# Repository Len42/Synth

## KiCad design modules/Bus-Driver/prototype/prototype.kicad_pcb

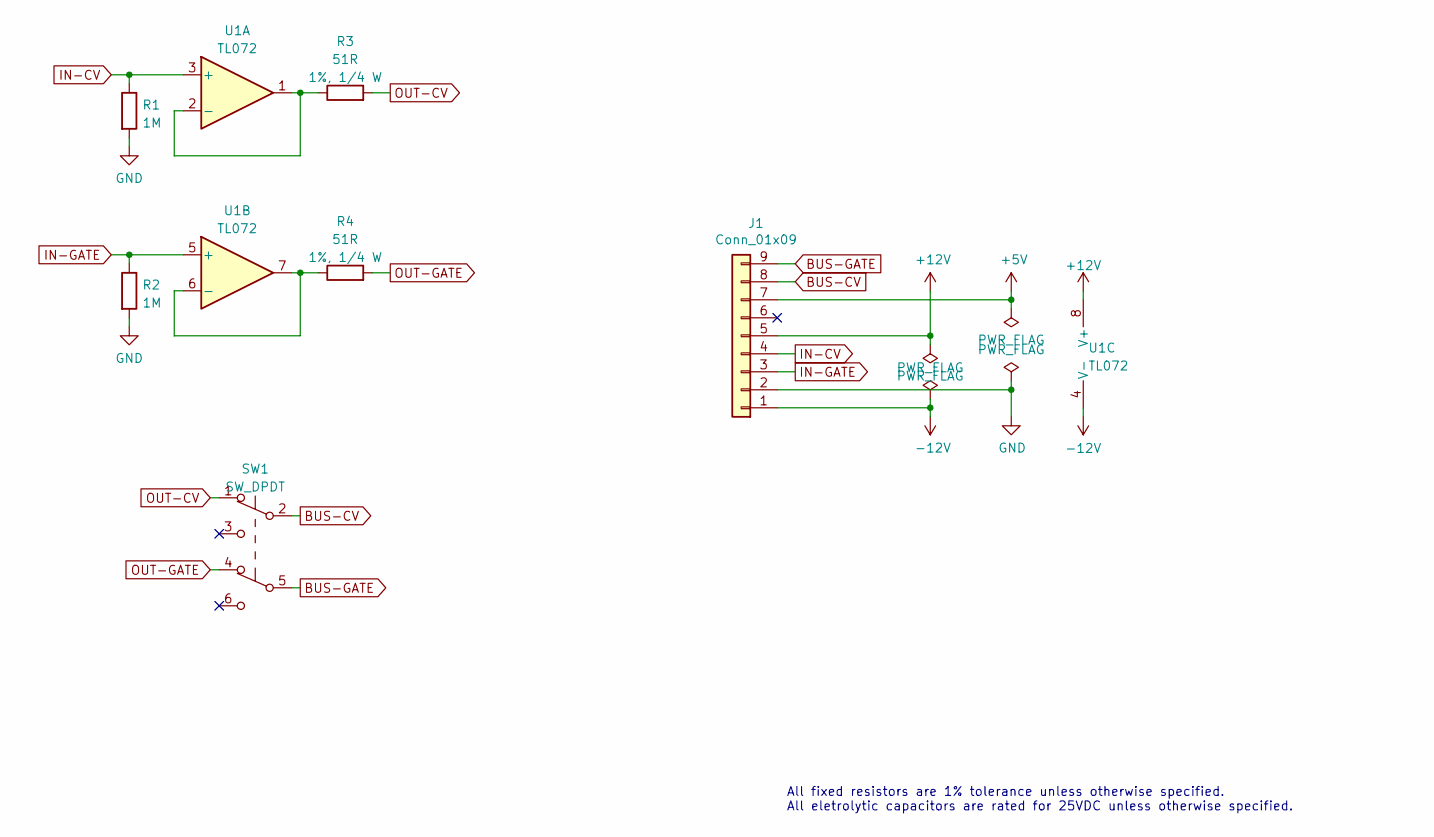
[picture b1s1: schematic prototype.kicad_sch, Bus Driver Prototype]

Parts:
J1: Conn_01x09; PinHeader_1x09_P2.54mm_Vertical
R1, R2: 1M; R_Axial_DIN0207_L6.3mm_D2.5mm_P7.62mm_Horizontal; ManufacturerPartNum MFR-12*
R3, R4: 51R; R_Axial_DIN0207_L6.3mm_D2.5mm_P10.16mm_Horizontal; ManufacturerPartNum MFR-25FBF52-51R
SW1: SW_DPDT; SW_DPDT_THT_2.54; ManufacturerPartNum 2S1-MDP1-T1-B1-M2QE
U1: TL072; DIP-8_W7.62mm; ManufacturerPartNum TL072BCP

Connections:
+5V: J1.7
+12V: J1.5, U1.8 (V+)
-12V: J1.1, U1.4 (V-)
BUS-CV: J1.8, SW1.2 (B)
BUS-GATE: J1.9, SW1.5 (B)
GND: J1.2, R1.2, R2.2
IN-CV: J1.4, R1.1, U1.3 (+)
IN-GATE: J1.3, R2.1, U1.5 (+)
unnamed: R3.1, U1.1, U1.2 (-)
unnamed: R4.1, U1.6 (-), U1.7
OUT-CV: R3.2, SW1.1 (A)
OUT-GATE: R4.2, SW1.4 (A)

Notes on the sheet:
All fixed resistors are 1% tolerance unless otherwise specified. All eletrolytic capacitors are rated for 25VDC unless otherwise specified.

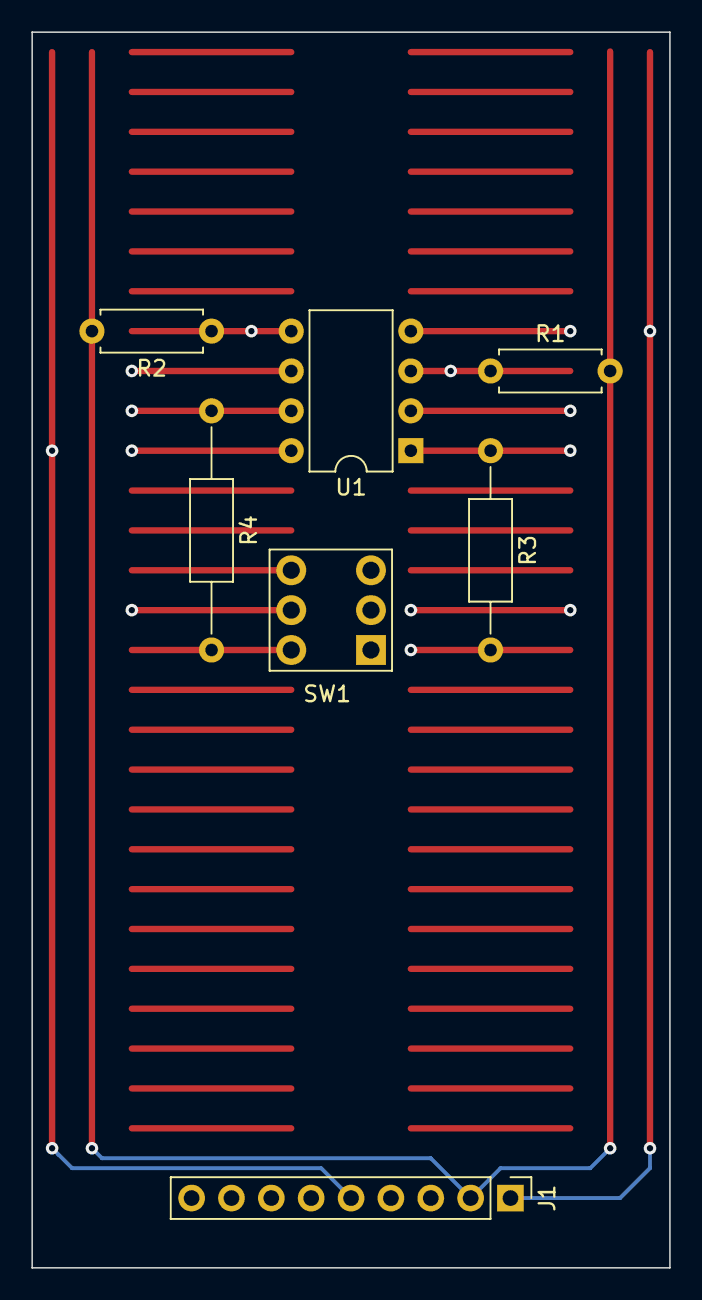
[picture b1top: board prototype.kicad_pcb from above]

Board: 6 copper layers, 40.6 x 78.7 mm, 7 parts (0 on the bottom side), 11 nets.

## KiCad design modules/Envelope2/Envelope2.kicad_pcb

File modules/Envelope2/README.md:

# Dual Envelope Generator

## 8HP Eurorack Module

### Features
- Two ADSR envelope generators
- Attack, decay, and release times range from very short (< 1 millisecond) to approx. 10 seconds
- Envelopes are switchable between linear and logarithmic curves
- Gate input can default to the Eurorack bus gate line (jumper-selectable) - more info [here](https://lenp.net/synth/eurorack-bus-cv-gate.html)
- Channel 1 gate input is normalled to channel 2 so one gate signal can trigger both envelopes

### Notes
This module requires a 16-pin Eurorack power cable that supplies +5 V power in addition to +12 V and -12 V.

An Arduino-compatible ATmega328P microcontroller generates the envelopes. The firmware source code is in [firmware/Envelope2/Envelope2.ino](firmware/Envelope2/Envelope2.ino). MakeLookupTables is a program that generates data tables used in the firmware. See [here](https://lenp.net/synth/firmware-programming.html) for info about programming the firmware onto the microcontroller chip.

PCB layouts are provided in KiCad and gerber formats. A front panel design is included as a drilled PCB layout (with no labels or graphics).

The PCBs that I used can be ordered from OSH Park. The designs are here:
- [Front panel](https://oshpark.com/shared_projects/PnWXqRcs)
- [Controls board](https://oshpark.com/shared_projects/XBUi1v48)
- [Main board](https://oshpark.com/shared_projects/cbrPcghP) (Note: There is an error in this PCB which has been corrected in the current version of the KiCad & gerber files.)

Please note that I am a hobbyist, not a trained electronics engineer. No guarantees!

### Software Used

* [KiCad](https://www.kicad.org/) 6.0.0
* [Arduino](https://www.arduino.cc/) 1.8.18
* (optional) [Visual Studio 2019](https://visualstudio.microsoft.com/) - Only used to generate the numtables.h file, which is provided.

<hr /><div><div style="float:left; padding-right:10px;"></div><div style="xfloat:left; padding-left:10px;"><br />© 2022 Len Popp CC BY<br />This work is licensed under a <a rel="license" href="http://creativecommons.org/licenses/by/4.0/">Creative Commons Attribution 4.0 International License</a>.</div></div>

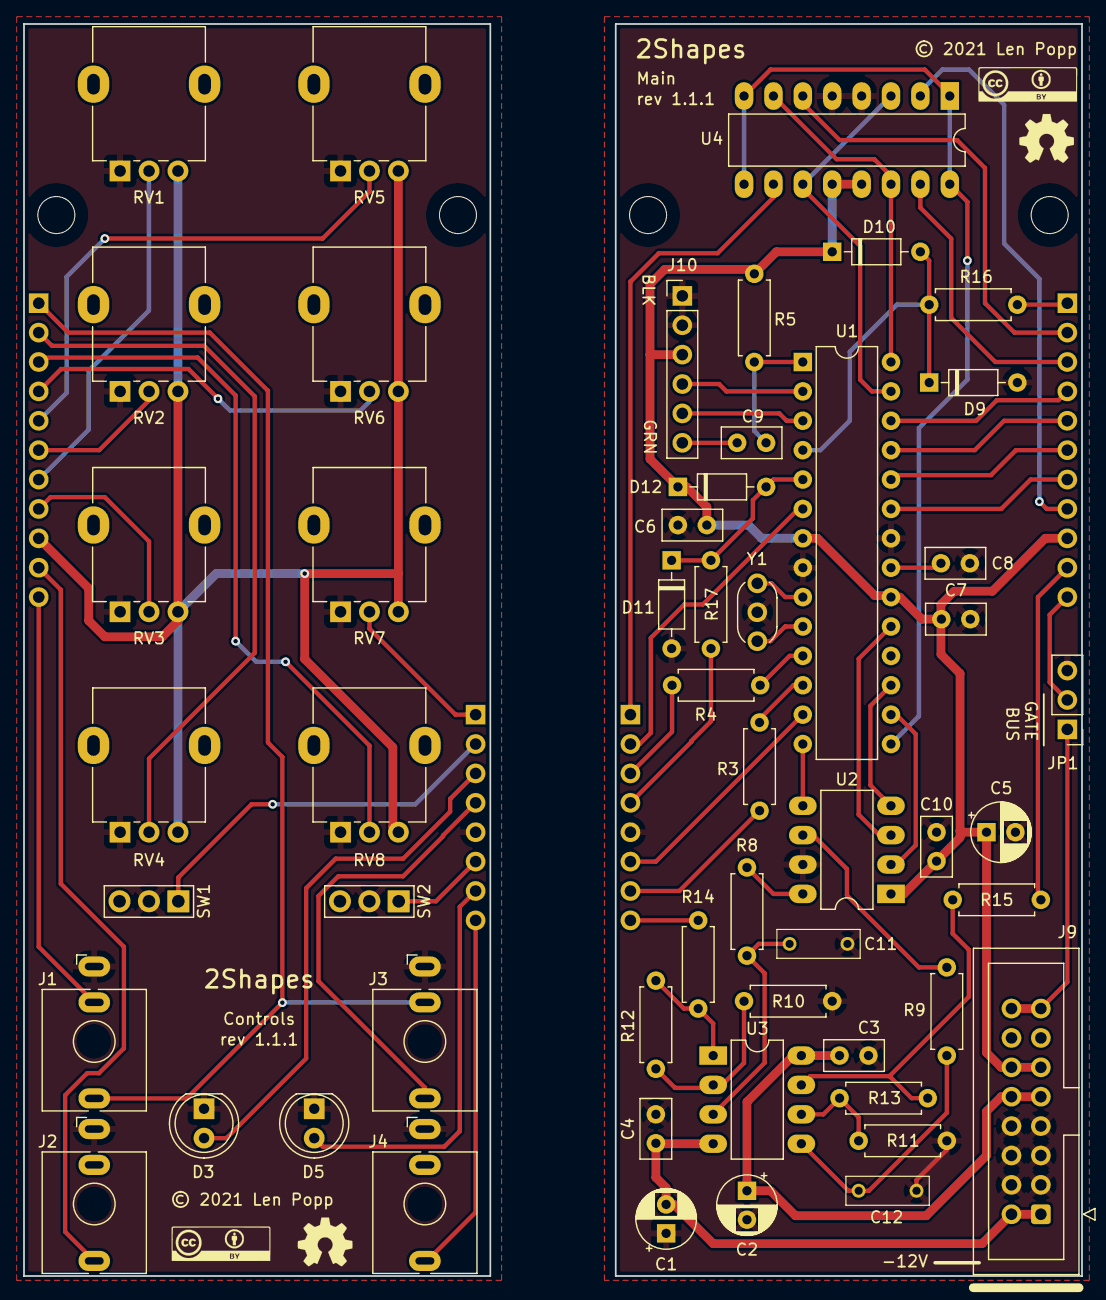
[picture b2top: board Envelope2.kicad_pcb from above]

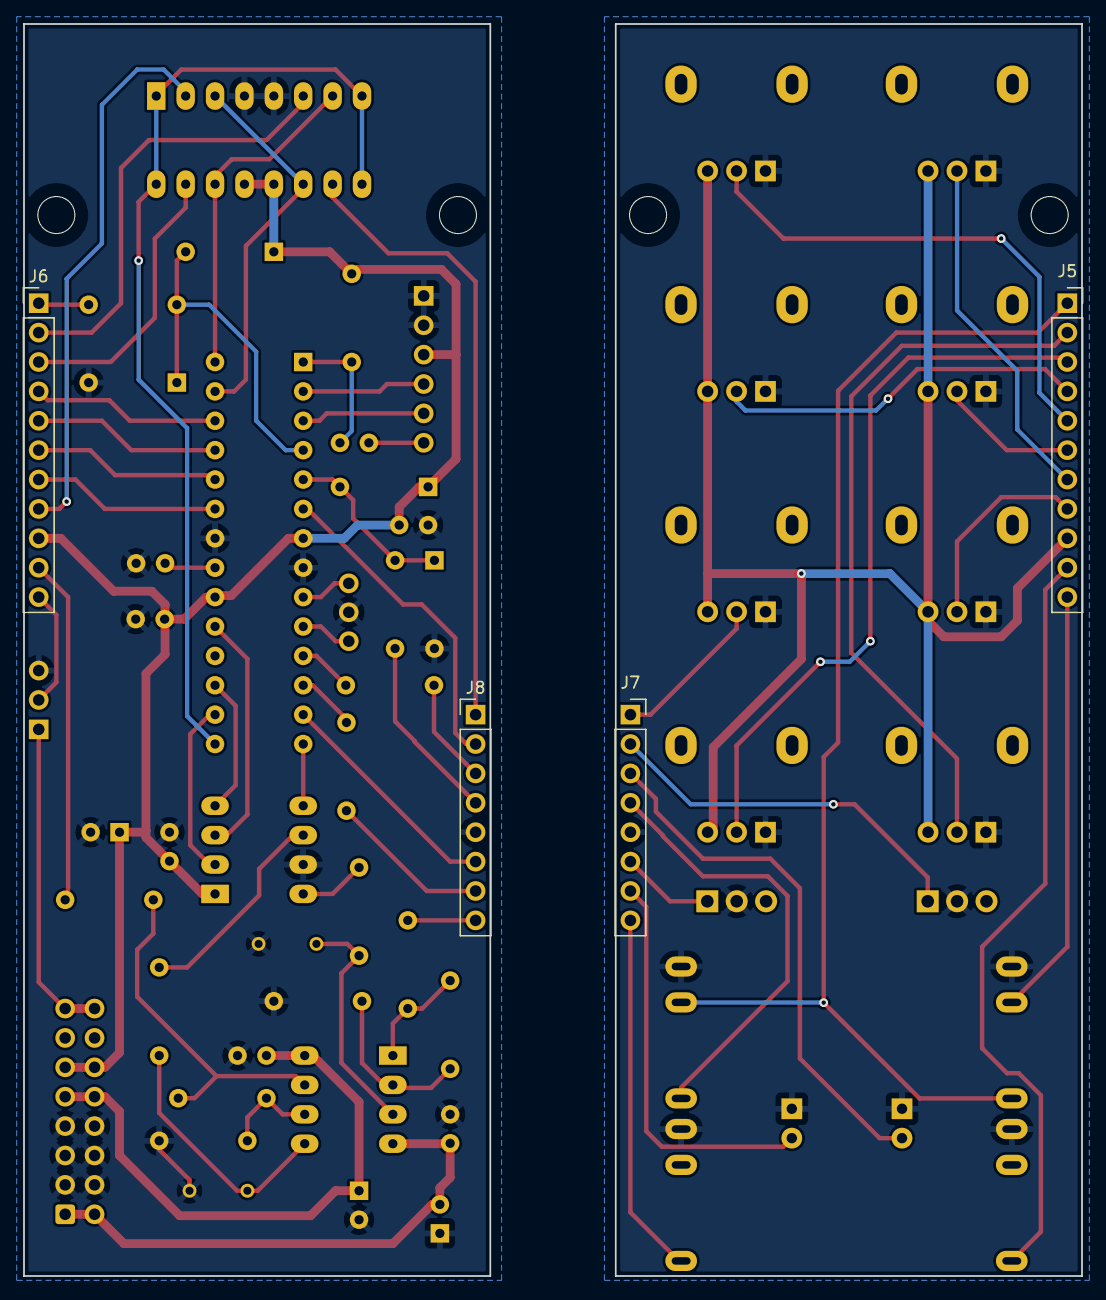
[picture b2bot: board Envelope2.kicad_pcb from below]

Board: 2 copper layers, 91.4 x 108.2 mm, 65 parts (4 on the bottom side), 48 nets.

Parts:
C1, C2, C5: 10U; CP_Radial_D5.0mm_P2.50mm
C3, C4, C6, C7, C8, C9, C10: 100N; C_Disc_D5.0mm_W2.5mm_P2.50mm
C11, C12: 3N3; C_Rect_Kemet_L7.2mm_W2.5mm_P5mm
D3, D5: LED_5mm_Blue; LED_D5.0mm
D9, D10, D11, D12: 1N5711; D_DO-35_SOD27_P7.62mm_Horizontal
G1, G2: Logo_CC_BY
G3, G4: Logo_OSHW
H1, H2, H3, H4: MountingHole_M3; MountingHole_PCB_3.2mm_M3
J1, J2, J3, J4: WQP-PJ398; Jack_3.5mm_QingPu_WQP-PJ398SM_Vertical
J5: Conn_Front_Left_Top; PinSocket_1x11_P2.54mm_Vertical
J6: Conn_Back_Right_Top; PinHeader_1x11_P2.54mm_Vertical
J7: Conn_Front_Right; PinSocket_1x08_P2.54mm_Vertical
J8: Conn_Back_Left; PinHeader_1x08_P2.54mm_Vertical
J9: Conn_Eurorack_16; IDC-Header-Eurorack-16-TH
J10: FTDI; PinHeader_1x06_P2.54mm_Vertical
JP1: GATE-BUS; PinHeader_1x03_P2.54mm_Vertical
R3, R4: 270R; R_Axial_DIN0207_L6.3mm_D2.5mm_P7.62mm_Horizontal
R5: 10K; R_Axial_DIN0207_L6.3mm_D2.5mm_P7.62mm_Horizontal
R8, R9: 24K; R_Axial_DIN0207_L6.3mm_D2.5mm_P7.62mm_Horizontal
R10, R11, R12, R13: 47K; R_Axial_DIN0207_L6.3mm_D2.5mm_P7.62mm_Horizontal
R14, R15: 51R; R_Axial_DIN0207_L6.3mm_D2.5mm_P7.62mm_Horizontal
R16, R17: 100K; R_Axial_DIN0207_L6.3mm_D2.5mm_P7.62mm_Horizontal
RV1, RV2, RV3, RV4, RV5, RV6, RV7, RV8: 100K; Potentiometer_Alpha_RD901F-40-00D_Single_Vertical
SW1, SW2: SPDT; SW_SPDT_THT_2.54
U1: ATmega328P-PU; DIP-28_W7.62mm
U2: MCP4822; DIP-8_W7.62mm_LongPads
U3: TL072; DIP-8_W7.62mm_LongPads
U4: DG413; DIP-16_W7.62mm_LongPads
Y1: 16MHz; Resonator_muRata_CSTLSxxxX-3Pin_W5.5mm_H3.0mm

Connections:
+5V: C5.1, C6.1, C7.1, C10.2, D10.1 (K), D12.1 (K), J5.9, J6.9, J9.11 (+5V), J9.12, J10.3 (VCC), R5.1, RV1.3, RV2.3, RV3.3, RV4.3, RV5.3, RV6.3, RV7.3, RV8.3, U1.7 (VCC), U1.20 (AVCC), U2.1 (Vdd), U4.12 (VL), U4.13 (V+)
+12V: C2.1, C3.1, J9.9 (+12V), J9.10, U3.8 (V+)
-12V: C1.2, C4.2, J9.1 (-12V), J9.2, U3.4 (V-)
/Main/ADC-SEL: U1.15 ((PCINT1/OC1A/PB1)d9), U4.1, U4.8, U4.9, U4.16
/Main/SPI-MOSI: U1.17 ((PCINT3/OC2A/MOSI/PB3)d11), U2.4 (SDI)
/Main/SPI-SCLK: U1.19 ((PCINT5/SCK/PB5)d13), U2.3 (SCK)
/Main/UART_RX: J10.4 (TXO), U1.2 ((PCINT16/RXD/PD0)d0)
/Main/UART_TX: J10.5 (RXI), U1.3 ((PCINT17/TXD/PD1)d1)
/Main/~LDAC: U1.14 ((PCINT0/CLKO/ICP1/PB0)d8), U2.5 (~LDAC)
/Main/~RESET: C9.2, R5.2, U1.1 ((PCINT14/~RESET/)PC6)
/Main/~SPI-CS: U1.16 ((PCINT2/OC1B/~SS/PB2)d10), U2.2 (~CS)
GATE-1: D9.1 (K), D10.2 (A), R16.1, U1.4 ((PCINT18/INT0/PD2)d2)
GATE-2: D11.1 (K), D12.2 (A), R17.1, U1.5 ((PCINT19/OC2B/INT1/PD3)d3)
GND: C1.1, C2.2, C3.2, C4.1, C5.2, C6.2, C7.2, C8.2, C10.1, C11.2, C12.2, D3.1 (K), D5.1 (K), D9.2 (A), D11.2 (A), J1.S, J2.S, J3.S, J4.S, J7.5, J8.5, J9.3 (GND), J9.4, J9.5 (GND), J9.6, J9.7 (GND), J9.8, J10.1 (GND), J10.2 (CTS), JP1.3 (B), R10.2, R11.2, RV1.1, RV2.1, RV3.1, RV4.1, RV5.1, RV6.1, RV7.1, RV8.1, SW1.2 (B), SW2.2 (B), U1.8 (GND), U1.22 (GND), U2.7 (Vss), U4.4 (V-), U4.5 (GND), Y1.2
IN-GATE-1: J1.T, J3.TN, J5.1, J6.1, R16.2
IN-GATE-2: J3.T, J7.4, J8.4, R17.2
IN-GATE-BUS: J1.TN, J5.11, J6.11, JP1.2 (C)
IN-POT-A-1: J5.7, J6.7, RV1.2, U1.23 ((PCINT8/ADC0/PC0)a0)
IN-POT-A-2: J5.5, J6.5, RV5.2, U1.25 ((PCINT10/ADC2/PC2)a2)
IN-POT-D-1: J5.6, J6.6, RV2.2, U1.24 ((PCINT9/ADC1/PC1)a1)
IN-POT-D-2: J5.4, J6.4, RV6.2, U1.26 ((PCINT11/ADC3/PC3)a3)
IN-POT-R-1: J5.2, J6.2, RV4.2, U4.6
IN-POT-R-2: J5.3, J6.3, RV8.2, U4.15
IN-POT-R-BOTH: U1.28 ((PCINT13/SCL/ADC5/PC5)a5), U4.7, U4.14
IN-POT-S-1: J5.8, J6.8, RV3.2, U4.2
IN-POT-S-2: J7.1, J8.1, RV7.2, U4.10
IN-POT-S-BOTH: U1.27 ((PCINT12/SDA/ADC4/PC4)a4), U4.3, U4.11
IN-SW-LOGLIN-1: J7.2, J8.2, SW1.1 (A), U1.6 ((PCINT20/XCK/T0/PD4)d4)
IN-SW-LOGLIN-2: J7.6, J8.6, SW2.1 (A), U1.13 ((PCINT23/AIN1/PD7)d7)
LED-1: D3.2 (A), J7.3, J8.3, R4.2
LED-2: D5.2 (A), J7.7, J8.7, R3.2
unnamed: C8.1, U1.21 (AREF)
unnamed: C9.1, J10.6 (DTR)
unnamed: C11.1, R8.1, U3.3 (+)
unnamed: C12.1, R9.1, U3.5 (+)
unnamed: J9.15 (GATE), J9.16, JP1.1 (A)
unnamed: R3.1, U1.12 ((PCINT22/OC0A/AIN0/PD6)d6)
unnamed: R4.1, U1.11 ((PCINT21/OC0B/T1/PD5)d5)
unnamed: R8.2, U2.8 (VA)
unnamed: R9.2, U2.6 (VB)
unnamed: R10.1, R12.2, U3.2 (-)
unnamed: R11.1, R13.2, U3.6 (-)
unnamed: R12.1, R14.2, U3.1
unnamed: R13.1, R15.2, U3.7
unnamed: U1.9 ((PCINT6/TOSC1/PB6)XTAL1), Y1.3
unnamed: U1.10 ((PCINT7/TOSC2/PB7)XTAL2), Y1.1
OUT-1: J2.T, J5.10, J6.10, R15.1
OUT-2: J4.T, J7.8, J8.8, R14.1

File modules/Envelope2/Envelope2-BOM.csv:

Ref,Qty,Value,Value2,Note,Description,Datasheet,Manufacturer,ManuPartNum,Distributor1,DistributorPartNum1,DistributorPartLink1,Distributor2,DistributorPartNum2,DistributorPartLink2,Distributor3,DistributorPartNum3,DistributorPartLink3
A1,1,Cable_Eurorack_16,,Length as required,Eurorack 16-16 pin power & bus cable,,,,Thonk,,https://www.thonk.co.uk/shop/eurorack-power-cables/,SynthCube,,https://synthcube.com/cart/eurorack-ribbon-power-cables,Modular Addict,,https://modularaddict.com/parts/eurorack-power-cables-1
C1 C2 C5,3,10U,25 VDC,12 V decoupling,Capacitor - Electrolytic - 12 V decoupling,https://industrial.panasonic.com/cdbs/www-data/pdf/RDF0000/A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,Panasonic,EEA-FC1E100,Mouser,667-EEA-FC1E100,https://www.mouser.ca/ProductDetail/Panasonic/EEA-FC1E100?qs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,,,,,,
C3 C4 C6 C7 C8 C9 C10,7,100N,,IC decoupling,Capacitor - Ceramic - IC decoupling,,TDK,FG18X7R1H104KNT06,Mouser,810-FG18X7R1H104KNT6,https://www.mouser.ca/ProductDetail/810-FG18X7R1H104KNT6,,,,,,
C11 C12,2,3N3,,,Capacitor - Film,https://www.mouser.ca/datasheet/2/212/F3294_MMK-1101858.pdf,KEMET,MMK5102J100J01L16.5TA18,Mouser,80-MMK5102J100J1TA18,https://www.mouser.ca/ProductDetail/KEMET/MMK5102J100J01L165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,,,,,,
D3 D5,2,LED_5mm_Blue,,,Blue Light Emitting Diode,https://www.mouser.ca/datasheet/2/423/VAOL-5LSBY1-1064871.pdf,VCC,VAOL-5LSBY1,Mouser,593-VAOL-5LSBY1,https://www.mouser.ca/ProductDetail/VCC/VAOL-5LSBY1?qs=sGAEp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,,,,,,
D9 D10 D11 D12,4,1N5711,,,Schottky signal diode,https://www.mouser.ca/datasheet/2/389/cd00000759-1795802.pdf,STMicroelectronics,1N5711,Mouser,511-1N5711,https://www.mouser.ca/ProductDetail/STMicroelectronics/1N571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,,,,,,
H5 H7 H8 H10,4,HW_Screw_M3x0.50x6,,,"Machine screw, M3x0.50x6",,,,,,,,,,,,
H6 H9,2,HW_Standoff_F-F_11mm_M3x0.50,,,"Standoff, 11mm, female-female, M3x0.50",https://www.thonk.co.uk/wp-content/uploads/2018/05/standoff-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,Ettinger,05.03.111,Thonk,Mech_11mm_Standoff_(x10),https://www.thonk.co.uk/shop/standoffs/,Mouser,710-970110321,https://www.mouser.ca/ProductDetail/Wurth-Elektronik/9701103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,,,
H11,1,Jumper_2,,,"Jumper connector, 2-pin socket",https://www.mouser.ca/datasheet/2/209/KC-301174-1171759.pdf,,,Mouser,151-8013-E,https://www.mouser.ca/ProductDetail/Kobiconn/151-8013-E?qs=R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,Adafruit,3525,https://www.adafruit.com/product/3525,,,
J1 J2 J3 J4,4,WQP-PJ398,,,"Audio Jack, 2 Poles (Mono / TS), Switched T Pole (Normalling), QingPu / Thonkiconn",http://www.qingpu-electronics.com/en/products/WQP-PJ398SM-362.html,QingPu / Thonk,PJ398SM / WQP518MA,Thonk,PJ398SM,https://www.thonk.co.uk/shop/thonkiconn/,SynthCube,WQP518MA,https://synthcube.com/cart/3-5mm-euro-jacks,Adafruit,4031,https://www.adafruit.com/product/4031
J5,1,Conn_Front_Left_Top,,,"Generic connector, single row, 01x11, script generated (kicad-library-utils/schlib/autogen/connector/)",https://www.mouser.ca/datasheet/2/527/ssq_th-2854703.pdf,Samtec,SSQ-111-01-T-S,Mouser,200-SSQ11101TS,https://www.mouser.ca/ProductDetail/Samtec/SSQ-111-01-T-S?qs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,Adafruit,598,https://www.adafruit.com/product/598,,,
J6,1,Conn_Back_Right_Top,,,"Generic connector, single row, 01x11, script generated (kicad-library-utils/schlib/autogen/connector/)",https://www.mouser.ca/datasheet/2/18/1/bwb_bergstik-2584943.pdf,Amphenol FCI,68001-411HLF,Mouser,649-68001-411HLF,https://www.mouser.ca/ProductDetail/Amphenol-FCI/68001-411HL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,Adafruit,392,https://www.adafruit.com/product/392,,,
J7,1,Conn_Front_Right,,,"Generic connector, single row, 01x08, script generated (kicad-library-utils/schlib/autogen/connector/)",https://www.mouser.ca/datasheet/2/595/Gravitech_8Fx1_254mm-2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,Gravitech,8Fx1-254mm,Mouser,992-8FX1-254MM,https://www.mouser.ca/ProductDetail/Gravitech/8Fx1-254mm?qs=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,,,,,,
J8,1,Conn_Back_Left,,,"Generic connector, single row, 01x08, script generated (kicad-library-utils/schlib/autogen/connector/)",https://www.amphenol-icc.com/media/wysiwyg/files/documentati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,Amphenol FCI,10129378-908001BLF,Mouser,649-1012937890801BLF,https://www.mouser.ca/ProductDetail/Amphenol-FCI/10129378-90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,,,,,,
J9,1,Conn_Eurorack_16,,,Eurorack 16-pin board power/CV/gate bus connector,https://www.mouser.ca/datasheet/2/445/61201621621-1717735.pdf,Wurth Elektronik,61201621621,Mouser,710-61201621621,https://www.mouser.ca/ProductDetail/Wurth-Elektronik/6120162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,,,,,,
J10,1,FTDI,,,Pin header for FTDI USB-serial cable,https://www.amphenol-icc.com/media/wysiwyg/files/documentati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,Amphenol FCI,10129378-906001BLF,Mouser,649-1012937890601BLF,https://www.mouser.ca/ProductDetail/Amphenol-FCI/10129378-90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,,,,,,
JP1,1,GATE-BUS,,,"Jumper pins, 3-pole, pins 1+2 closed/bridged",,Amphenol FCI,10129378-903001BLF,Mouser,649-1012937890301BLF,https://www.mouser.ca/ProductDetail/?qs=0lQeLiL1qybuYTJnitum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,,,,,,
R3 R4,2,270R,"5%, 1/4 W",,Resistor,https://www.mouser.ca/datasheet/2/447/Yageo_LR_MFR_1-1714151.pdf,YAGEO,MFR-12FTF52-270R,Mouser,603-MFR-12FTF52-270R,https://www.mouser.ca/ProductDetail/YAGEO/MFR-12FTF52-270R?q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,,,,,,
R5,1,10K,,,Resistor,https://www.mouser.ca/datasheet/2/447/Yageo_LR_MFR_1-1714151.pdf,YAGEO,MFR-12FRF52-10K,Mouser,603-MFR-12FRF5210K,https://www.mouser.ca/ProductDetail/YAGEO/MFR-12FRF52-10K?qs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,,,,,,
R8 R9,2,24K,,,Resistor,https://www.mouser.ca/datasheet/2/447/Yageo_LR_MFR_1-1714151.pdf,YAGEO,MFR-12FTF52-30K,Mouser,603-MFR-12FTF52-30K,https://www.mouser.ca/ProductDetail/YAGEO/MFR-12FTF52-30K?qs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,,,,,,
R10 R11 R12 R13,4,47K,"1%, 1/6 W",,Resistor,https://www.mouser.ca/datasheet/2/447/Yageo_LR_MFR_1-1714151.pdf,YAGEO,MFR-12FTF52-47K,Mouser,603-MFR-12FTF52-47K,https://www.mouser.ca/ProductDetail/YAGEO/MFR-12FTF52-47K?qs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,,,,,,
R14 R15,2,51R,"5%, 1/4 W",Output limiting,Resistor,https://www.mouser.ca/datasheet/2/447/Yageo_LR_MFR_1-1714151.pdf,YAGEO,MFR-25FBF52-51R,Mouser,603-MFR-25FBF52-51R,https://www.mouser.ca/ProductDetail/?qs=oAGoVhmvjhzVx2bdEH1T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,,,,,,
R16 R17,2,100K,,,Resistor,https://www.mouser.ca/datasheet/2/447/Yageo_LR_MFR_1-1714151.pdf,YAGEO,MFR-12FRF52-10K,Mouser,603-MFR-12FRF5210K,https://www.mouser.ca/ProductDetail/YAGEO/MFR-12FRF52-10K?qs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,,,,,,
RV1 RV2 RV3 RV4 RV5 RV6 RV7 RV8,8,100K,LIN,,Potentiometer,https://www.mouser.ca/datasheet/2/13/alpha_taiwan_08192019_R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,Alpha,RD901F-40-15R1-B100K-00DL1,Thonk,Group_Pot_Alpha_6.35mm,https://www.thonk.co.uk/shop/alpha-9mm-pots/,Mouser,311-1940F-*,https://www.mouser.ca/c/passive-components/potentiometers-tr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,SynthCube,9MMALPHAPOTMSTR,https://synthcube.com/cart/alpha-9mm-potentiometer-right-ang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
SW1 SW2,2,SPDT,,,Single Pole Single Throw (SPST) sub-mini toggle switch,https://www.mouser.ca/datasheet/2/221/MS-100542-1173960.pdf,Mountain Switch,10TC410,Mouser,10TC410,https://www.mouser.ca/ProductDetail/Mountain-Switch/10TC410?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,Thonk,,https://www.thonk.co.uk/shop/sub-mini-toggle-switches/,SynthCube,,https://synthcube.com/cart/toggle-switch-submini-pc-pin
U1,1,ATmega328P-PU,,16 MHz,"AVR Microcontroller, 8-bit, 20MHz, 32kB Flash, 2kB SRAM, 1kB EEPROM, DIP-28",https://www.microchip.com/en-us/product/ATmega328P,Microchip,ATMEGA328P-PU,Mouser,556-ATMEGA328P-PU,https://www.mouser.ca/ProductDetail/?qs=K8BHR703ZXguOQv3sKbW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,,,,,,
U2,1,MCP4822,,,2-Channel 12-Bit D/A Converters with SPI Interface and Internal Reference (2.048V),https://www.mouser.ca/datasheet/2/268/21953a-8929.pdf,Microchip,MCP4822-E/P,Mouser,579-MCP4822-E/P,https://www.mouser.ca/ProductDetail/Microchip-Technology/MCP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,,,,,,
U3,1,TL072,,,"Dual Low-Noise JFET-Input Operational Amplifiers, DIP-8/SOIC-8",https://www.ti.com/lit/ds/symlink/tl072b.pdf?ts=1628812694194,Texas Instruments,TL072BCP,Mouser,595-TL072BCP,https://www.mouser.ca/ProductDetail/Texas-Instruments/TL072B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,,,,,,
U4,1,DG413,,,"Quad SPST Monolithic CMOS Analog Switches, normally 2xON + 2xOFF, 17Ohm Ron, DIP-16",https://www.mouser.ca/datasheet/2/698/REN_dg411_12_13_DST_19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,Renesas / Intersil,DG413DJZ,Mouser,968-DG413DJZ,https://www.mouser.ca/ProductDetail/968-DG413DJZ,,,,,,
Y1,1,16MHz,,,"Three pin ceramic resonator, small symbol",https://www.mouser.ca/datasheet/2/281/p17e-1539077.pdf,Murata,CSTLS16M0X53Z-A0,Mouser, 81-CSTLS16M0X53Z-A0,https://www.mouser.ca/ProductDetail/?qs=x6vGwhDZZUZCi2wdIsDb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,,,,,,

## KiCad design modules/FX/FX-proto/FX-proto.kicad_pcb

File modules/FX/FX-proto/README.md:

# Digital Effects Module Prototype

## 8HP Eurorack Module

### Features
- [features]

### Notes
[notes]

This module requires a 16-pin Eurorack power cable, but it does not depend on +5V power from the Eurorack system.

PCB layouts are provided in KiCad and gerber formats. A PCB layout for a drilled front panel (with no labels) is also included.

(TBD) The PCBs that I used can be ordered from OSH Park. The designs are here:
- [Controls board](https://oshpark.com/shared_projects/zzz)
- [Middle board](https://oshpark.com/shared_projects/zzz)
- [Back board](https://oshpark.com/shared_projects/zzz)

Please note that I am a hobbyist, not a trained electronics engineer. No guarantees!

### Software Used

* [KiCad](https://www.kicad.org/) 6.0.6

<hr /><div><div style="float:left; padding-right:10px;"></div><div style="xfloat:left; padding-left:10px;"><br />© 2022 Len Popp CC BY<br />This work is licensed under a <a rel="license" href="http://creativecommons.org/licenses/by/4.0/">Creative Commons Attribution 4.0 International License</a>.</div></div>

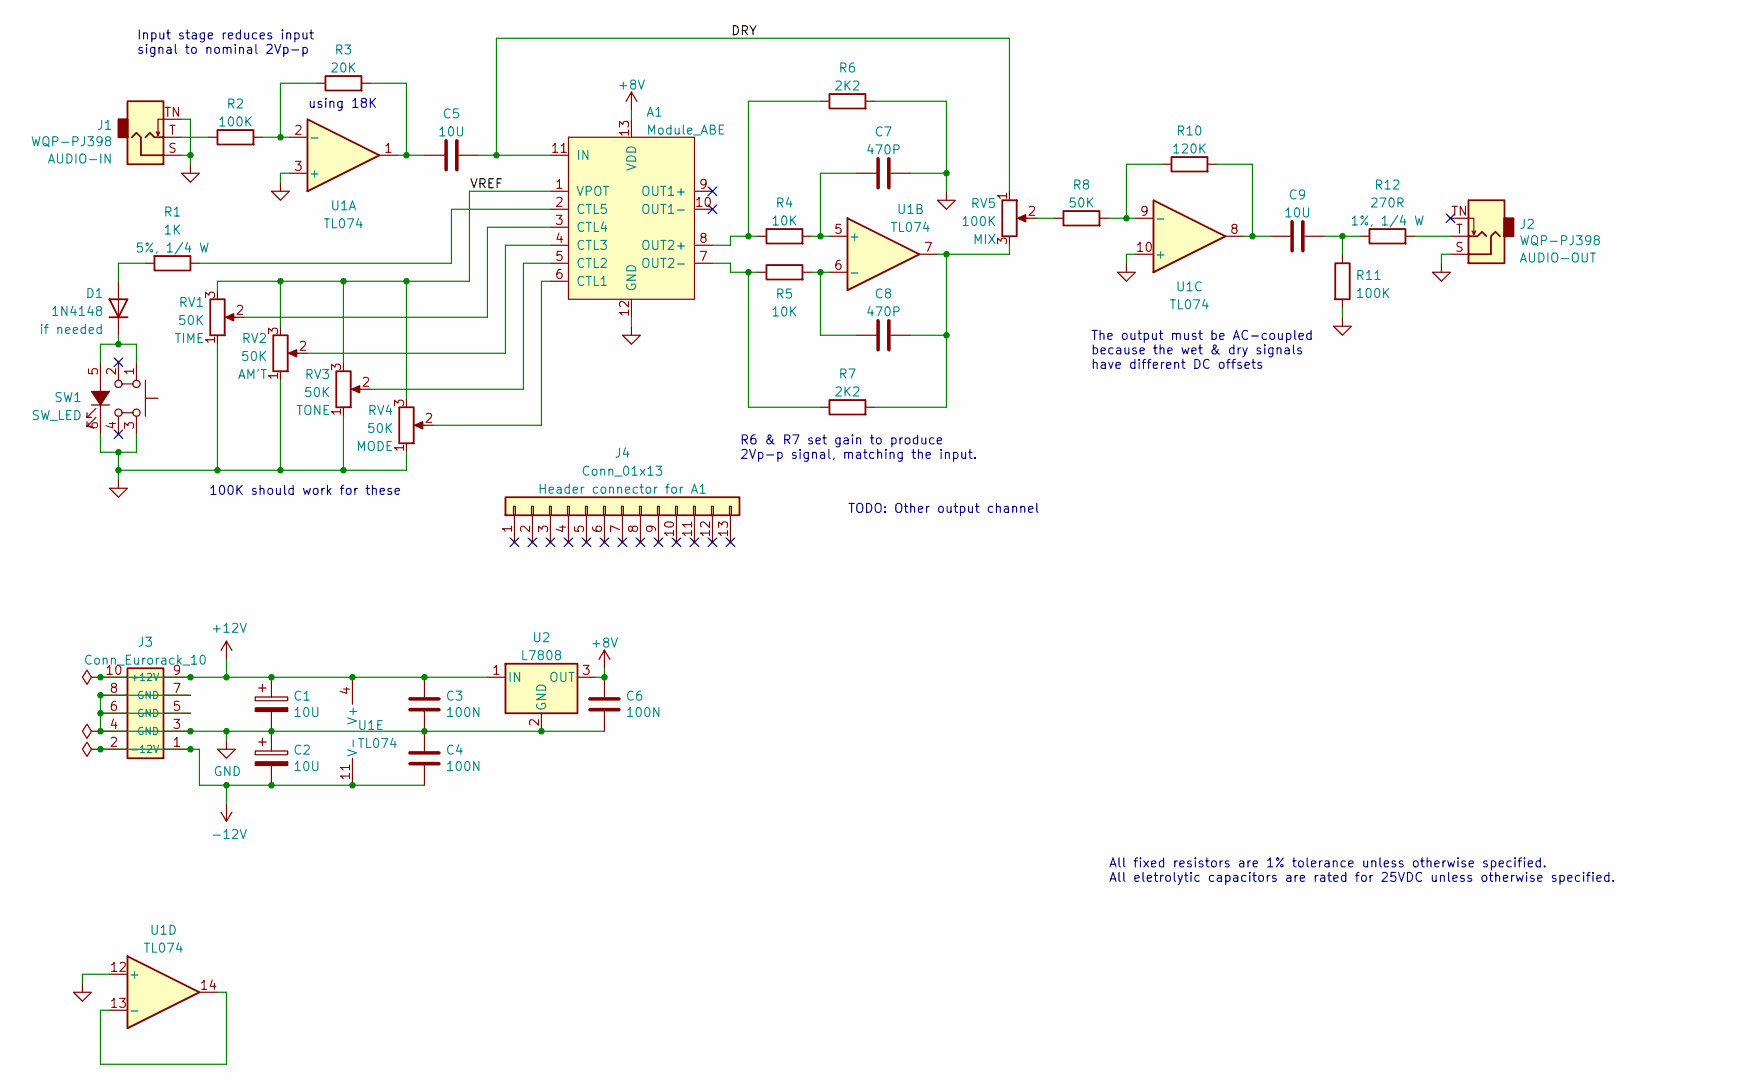
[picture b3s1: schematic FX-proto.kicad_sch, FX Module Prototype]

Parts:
A1: Module_ABE; Module_ABE_Socket_Vert; ManufacturerPartNum ABE
C1, C2: 10U; CP_Radial_D5.0mm_P2.50mm; ManufacturerPartNum ECE-A1VKS100I
C3, C4, C6: 100N; C_Disc_D5.0mm_W2.5mm_P2.50mm; ManufacturerPartNum FG18X7R1H104KNT06
C5, C9: 10U; C_Radial_D5.0mm_H5.0mm_P2.50mm; ManufacturerPartNum ECE-A1EN100UI
C7, C8: 470P; C_Disc_D5.0mm_W2.5mm_P2.50mm
D1: 1N4148; D_DO-35_SOD27_P7.62mm_Horizontal; ManufacturerPartNum 1N4148-T50R
J1, J2: WQP-PJ398; Jack_3.5mm_QingPu_WQP-PJ398SM_Vertical; ManufacturerPartNum PJ398SM / WQP518MA
J3: Conn_Eurorack_10; IDC-Header-Eurorack-10-TH; ManufacturerPartNum 61201021621
J4: Conn_01x13
R1: 1K; R_Axial_DIN0207_L6.3mm_D2.5mm_P10.16mm_Horizontal; ManufacturerPartNum CCF071K00JKE36
R2, R11: 100K; R_Axial_DIN0207_L6.3mm_D2.5mm_P7.62mm_Horizontal; ManufacturerPartNum MFR-12*
R3: 20K; R_Axial_DIN0207_L6.3mm_D2.5mm_P7.62mm_Horizontal; ManufacturerPartNum MFR-12*
R4, R5: 10K; R_Axial_DIN0207_L6.3mm_D2.5mm_P7.62mm_Horizontal; ManufacturerPartNum MFR-12*
R6, R7: 2K2; R_Axial_DIN0207_L6.3mm_D2.5mm_P7.62mm_Horizontal; ManufacturerPartNum MFR-12*
R8: 50K; R_Axial_DIN0207_L6.3mm_D2.5mm_P10.16mm_Horizontal; ManufacturerPartNum MFR-12*
R10: 120K; R_Axial_DIN0207_L6.3mm_D2.5mm_P7.62mm_Horizontal; ManufacturerPartNum MFR-12*
R12: 270R; R_Axial_DIN0207_L6.3mm_D2.5mm_P10.16mm_Horizontal; ManufacturerPartNum MFR-25FRF52-270R
RV1, RV2, RV3, RV4: 50K; Potentiometer_SongHuei_Single_Vertical; ManufacturerPartNum R0904N*
RV5: 100K; Potentiometer_SongHuei_Single_Vertical; ManufacturerPartNum R0904N*
SW1: SW_LED; SW_Push_LED_C&K_D6R; ManufacturerPartNum D6RLBUF1 LFS
U1: TL074; DIP-14_W7.62mm; ManufacturerPartNum TL074BCN
U2: L7808; TO-220-3_Vertical

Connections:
+8V: A1.13 (VDD), C6.1, U2.3 (OUT)
+12V: C1.1, C3.1, J3.9 (+12V), J3.10, U1.4 (V+), U2.1 (IN)
-12V: C2.2, C4.2, J3.1 (-12V), J3.2, U1.11 (V-)
/DRY: A1.11 (IN), C5.2, RV5.1
/VREF: A1.1 (VPOT), RV1.3, RV2.3, RV3.3, RV4.3
GND: A1.12 (GND), C1.2, C2.1, C3.2, C4.1, C6.2, C7.2, J1.S, J1.TN, J2.S, J3.3 (GND), J3.4, J3.5 (GND), J3.6, J3.7 (GND), J3.8, R6.2, R11.2, RV1.1, RV2.1, RV3.1, RV4.1, SW1.3, SW1.6 (K), U1.3 (+), U1.10 (+), U1.12 (+), U2.2 (GND)
unnamed: A1.2 (CTL5), R1.1
unnamed: A1.3 (CTL4), RV1.2
unnamed: A1.4 (CTL3), RV2.2
unnamed: A1.5 (CTL2), RV3.2
unnamed: A1.6 (CTL1), RV4.2
unnamed: A1.7 (OUT2-), R5.1, R7.1
unnamed: A1.8 (OUT2+), R4.1, R6.1
unnamed: C5.1, R3.2, U1.1
unnamed: C7.1, R4.2, U1.5 (+)
unnamed: C8.1, R5.2, U1.6 (-)
unnamed: C8.2, R7.2, RV5.3, U1.7
unnamed: C9.1, R10.2, U1.8
unnamed: C9.2, R11.1, R12.1
unnamed: D1.1 (K), SW1.1, SW1.5 (A)
unnamed: D1.2 (A), R1.2
unnamed: J1.T, R2.1
unnamed: J2.T, R12.2
unnamed: R2.2, R3.1, U1.2 (-)
unnamed: R8.1, RV5.2
unnamed: R8.2, R10.1, U1.9 (-)
unnamed: U1.13 (-), U1.14

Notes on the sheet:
Input stage reduces input signal to nominal 2Vp-p
All fixed resistors are 1% tolerance unless otherwise specified. All eletrolytic capacitors are rated for 25VDC unless otherwise specified.
R6 & R7 set gain to produce 2Vp-p signal, matching the input.
100K should work for these
The output must be AC-coupled because the wet & dry signals have different DC offsets
TODO: Other output channel
using 18K

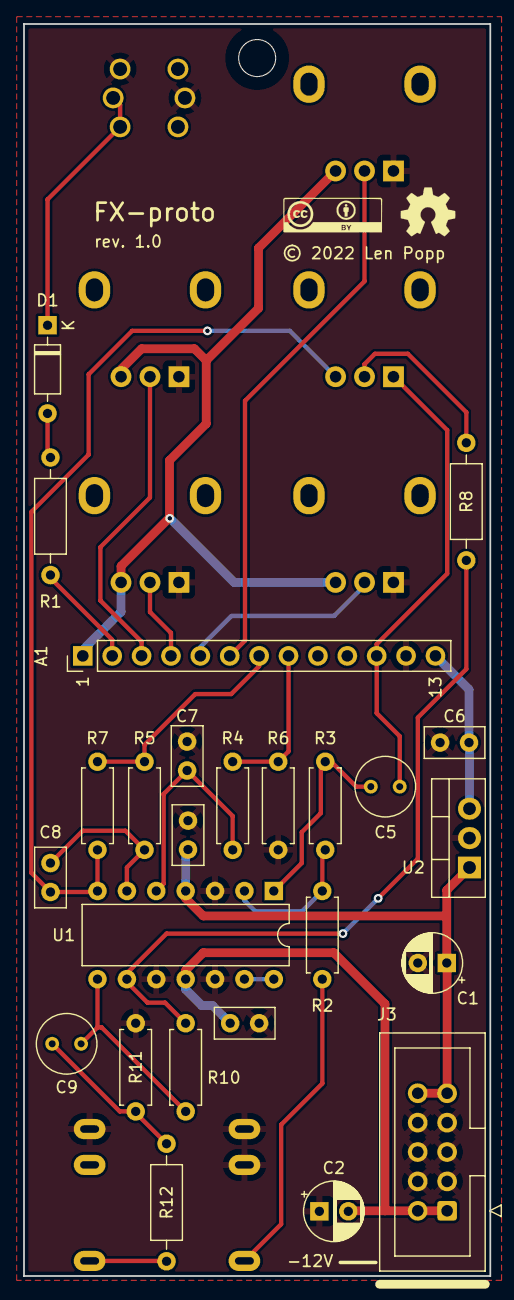
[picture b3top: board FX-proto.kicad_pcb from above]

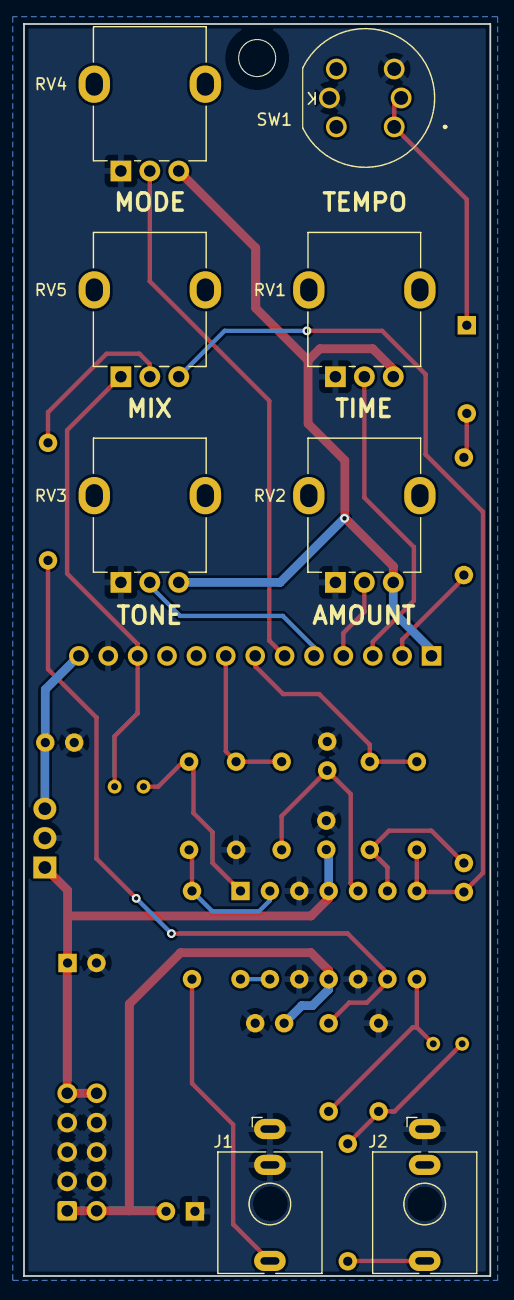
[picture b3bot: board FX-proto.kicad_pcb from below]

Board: 2 copper layers, 40.3 x 108.2 mm, 35 parts (8 on the bottom side), 27 nets.

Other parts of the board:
G1: Logo_CC_BY
G3: Logo_OSHW

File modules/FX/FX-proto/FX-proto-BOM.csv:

Ref,Qty,Value,Value2,Note,Description,Datasheet,Manufacturer,ManuPartNum,Distributor1,DistributorPartNum1,DistributorPartLink1,Distributor2,DistributorPartNum2,DistributorPartLink2,Distributor3,DistributorPartNum3,DistributorPartLink3
"A1","1","Module_ABE","","","Accu-Bell Effector digital effects module","https://www.tubesandmore.com/sites/default/files/associated_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","Accu-Bell","ABE","Antique Electronic Supply","P-R-ABE","https://www.tubesandmore.com/products/dsp-module-abe-accu-be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","","","","","",""
"C1 C2","2","10U","35 VDC","12 V decoupling","Capacitor - Electrolytic - 12 V decoupling","https://www.mouser.ca/datasheet/2/315/ABA0000C1059-947582.pdf","Panasonic","ECE-A1VKS100I","Mouser","667-ECE-A1VKS100I","https://www.mouser.ca/ProductDetail/667-ECE-A1VKS100I","Thonk","Group_Eurorack_DIY_Essential","https://www.thonk.co.uk/shop/eurorack-diy-essentials/","","",""
"C3 C4 C6","3","100N","","IC decoupling","Capacitor - Ceramic - IC decoupling","https://product.tdk.com/system/files/dam/doc/product/capacit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","TDK","FG18X7R1H104KNT06","Mouser","810-FG18X7R1H104KNT6","https://www.mouser.ca/ProductDetail/810-FG18X7R1H104KNT6","","","","","",""
"C5 C9","2","10U","","Non-polarized","Capacitor - Non-polarized Electrolytic","https://www.mouser.ca/datasheet/2/315/ABA0000C1053-947510.pdf","Panasonic","ECE-A1EN100UI","Mouser","667-ECE-A1EN100UI","https://www.mouser.ca/ProductDetail/Panasonic/ECE-A1EN100UI?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","","","","","",""
"C7 C8","2","470P","","","Capacitor - Ceramic","","","","","","","","","","","",""
"D1","1","1N4148","","if needed","Switching diode, 100V 0.15A, DO-35","https://www.mouser.ca/datasheet/2/308/1N914_D-2309448.pdf","On Semi / Fairchild","1N4148-T50R","Mouser","512-1N4148T50R","https://www.mouser.ca/ProductDetail/?qs=0lQeLiL1qyZS6rosZp7E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","","","","","",""
"J1 J2","2","WQP-PJ398","","","Audio Jack, 2 Poles (Mono / TS), Switched T Pole (Normalling), QingPu / Thonkiconn","http://www.qingpu-electronics.com/en/products/WQP-PJ398SM-362.html","QingPu / Thonk","PJ398SM / WQP518MA","Thonk","PJ398SM","https://www.thonk.co.uk/shop/thonkiconn/","SynthCube","WQP518MA","https://synthcube.com/cart/3-5mm-euro-jacks","Adafruit","4031","https://www.adafruit.com/product/4031"
"J3","1","Conn_Eurorack_10","","","Eurorack 10-pin board power connector","https://www.mouser.ca/datasheet/2/445/61201021621-1717731.pdf","Wurth Elektronik","61201021621","Mouser","710-61201021621","https://www.mouser.ca/ProductDetail/Wurth-Elektronik/6120102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","Thonk","","https://www.thonk.co.uk/shop/eurorack-diy-essentials/","","",""
"J4","1","Conn_01x13","","Header connector for A1","Generic connector, single row, 01x13, script generated (kicad-library-utils/schlib/autogen/connector/)","https://cdn-shop.adafruit.com/datasheets/00548.pdf","","","Adafruit","598","https://www.adafruit.com/product/598","Mouser","710-61303211821","https://www.mouser.ca/ProductDetail/Wurth-Elektronik/6130321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","","",""
"R1","1","1K","5%, 1/4 W","Output limiting","Resistor","https://www.mouser.ca/datasheet/2/427/ccf07-1762725.pdf","Vishay / Dale","CCF071K00JKE36","Mouser","71-CCF071K00JKE36","https://www.mouser.ca/ProductDetail/Vishay-Dale/CCF071K00JKE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","","","","","",""
"R2 R11","2","100K","1%, 1/6 W","","Resistor","https://www.mouser.ca/datasheet/2/447/Yageo_LR_MFR_1-1714151.pdf","YAGEO","MFR-12*","Mouser","603-MFR-12*","https://www.mouser.ca/c/?m=YAGEO&power+rating=166+mW+(1%2f6+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","","","","","",""
"R3","1","20K","1%, 1/6 W","","Resistor","https://www.mouser.ca/datasheet/2/447/Yageo_LR_MFR_1-1714151.pdf","YAGEO","MFR-12*","Mouser","603-MFR-12*","https://www.mouser.ca/c/?m=YAGEO&power+rating=166+mW+(1%2f6+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","","","","","",""
"R4 R5","2","10K","1%, 1/6 W","","Resistor","https://www.mouser.ca/datasheet/2/447/Yageo_LR_MFR_1-1714151.pdf","YAGEO","MFR-12*","Mouser","603-MFR-12*","https://www.mouser.ca/c/?m=YAGEO&power+rating=166+mW+(1%2f6+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","","","","","",""
"R6 R7","2","2K2","1%, 1/6 W","","Resistor","https://www.mouser.ca/datasheet/2/447/Yageo_LR_MFR_1-1714151.pdf","YAGEO","MFR-12*","Mouser","603-MFR-12*","https://www.mouser.ca/c/?m=YAGEO&power+rating=166+mW+(1%2f6+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","","","","","",""
"R8","1","50K","1%, 1/6 W","","Resistor","https://www.mouser.ca/datasheet/2/447/Yageo_LR_MFR_1-1714151.pdf","YAGEO","MFR-12*","Mouser","603-MFR-12*","https://www.mouser.ca/c/?m=YAGEO&power+rating=166+mW+(1%2f6+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","","","","","",""
"R10","1","120K","1%, 1/6 W","","Resistor","https://www.mouser.ca/datasheet/2/447/Yageo_LR_MFR_1-1714151.pdf","YAGEO","MFR-12*","Mouser","603-MFR-12*","https://www.mouser.ca/c/?m=YAGEO&power+rating=166+mW+(1%2f6+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","","","","","",""
"R12","1","270R","1%, 1/4 W","Output limiting","Resistor","https://www.mouser.ca/datasheet/2/447/Yageo_LR_MFR_1-1714151.pdf","YAGEO","MFR-25FRF52-270R","Mouser","603-MFR-25FRF52-270R","https://www.mouser.ca/ProductDetail/YAGEO/MFR-25FRF52-270R?q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","","","","","",""
"RV1 RV2 RV3 RV4","4","50K","","","Potentiometer","http://www.song-huei.com/proimages//eng/pdfimages/R0904N.pdf","Song Huei","R0904N*","SynthCube","SH9MMTPOTMSTR","https://synthcube.com/cart/9mm-trimmer-pots","Thonk","Group_SongHuei_TTP","https://www.thonk.co.uk/shop/ttpots/","","",""
"RV5","1","100K","","","Potentiometer","http://www.song-huei.com/proimages//eng/pdfimages/R0904N.pdf","Song Huei","R0904N*","SynthCube","SH9MMTPOTMSTR","https://synthcube.com/cart/9mm-trimmer-pots","Thonk","Group_SongHuei_TTP","https://www.thonk.co.uk/shop/ttpots/","","",""
"SW1","1","SW_LED","","","Push button switch with single LED, C&K D6R series","https://www.mouser.ca/datasheet/2/60/d6-1382571.pdf","C&K","D6RLBUF1 LFS","Mouser","611-D6RLBUF1LFS","https://www.mouser.co.uk/ProductDetail/CK/D6RLBUF1-LFS?qs=zW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","","","","","",""
"U1","1","TL074","","","Quad Low-Noise JFET-Input Operational Amplifiers, DIP-14/SOIC-14","http://www.ti.com/lit/ds/symlink/tl071.pdf","Texas Instruments","TL074BCN","Mouser","595-TL074BCN","https://www.mouser.ca/ProductDetail/?qs=vxEfx8VrU7BHurOY5iQd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","","","","","",""
"U2","1","L7808","","","Positive 1.5A 35V Linear Regulator, Fixed Output 8V, TO-220/TO-263/TO-252","http://www.st.com/content/ccc/resource/technical/document/da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","","","","","","","","","","",""

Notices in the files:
modules/Bus-Driver/prototype/prototype.kicad_pcb:
Copyright © 2022 Len Popp CC BY
modules/Envelope2/Envelope2.kicad_pcb:
© 2021 Len Popp
